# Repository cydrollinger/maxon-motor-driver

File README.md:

<a href="https://elec-real.com/case-studies/maxon-motor-driver/"></img></a>

>Electronic Realization L.L.C.								   
>Design: Maxon Motor Driver with Bluetooth v4.2/5.0		   
>Engineer: Cy Drollinger								   
>Date: 4/18												           
>Email: cy@elec-real.com
>Website: https://elec-real.com								   
>Address: 2023 Stadium Dr Suite 2B #210 Bozeman, MT 59715				   
>Phone: 406-539-8117	

**NOTE:**
 This case study has been tested and functions as specified. ER is a professional design house and monetary compensation is required for additional work toward this design enabling your monetary success, but conversation is welcome and appreciated toward improving any or all this design and its repository. 

 Think critically while operating and or redesigning this system. Open electronic circuitry can be dangerous due to easily shorting circuits which can generate immediate and intense heat resulting in fire. This is only one example of ill advised use. 			   

**PURPOSE:**
The puspose of this design was to implement a 3 phase DC motor driver for a high speed 8mm dia motor by
Maxon. The system utilizes the nRF52832 by Nordic Semicondutor which outputs bluetooth v4.2/5.0 wireless
communication. The device also boast the mpu9250 a 9 axis inertial sensor as well as a TDK's MEMs micro phone. 

>**File Arcitecture with a terse description**

* FOLDERS:
	* docs		: datasheets charging IC and battery holder
	* hardware	: eagle cadsoft(v7.7) hardware design files 	
		* library		: eagle part files 
		* manufacturing	: files required to produce the design
			* bom	: files created to order the parts	
			* gerber	: files generated to manufacture the board
			* <a href="https://oshpark.com/shared_projects/ryMoScdj"></img></a>
	* readme.md	: this file

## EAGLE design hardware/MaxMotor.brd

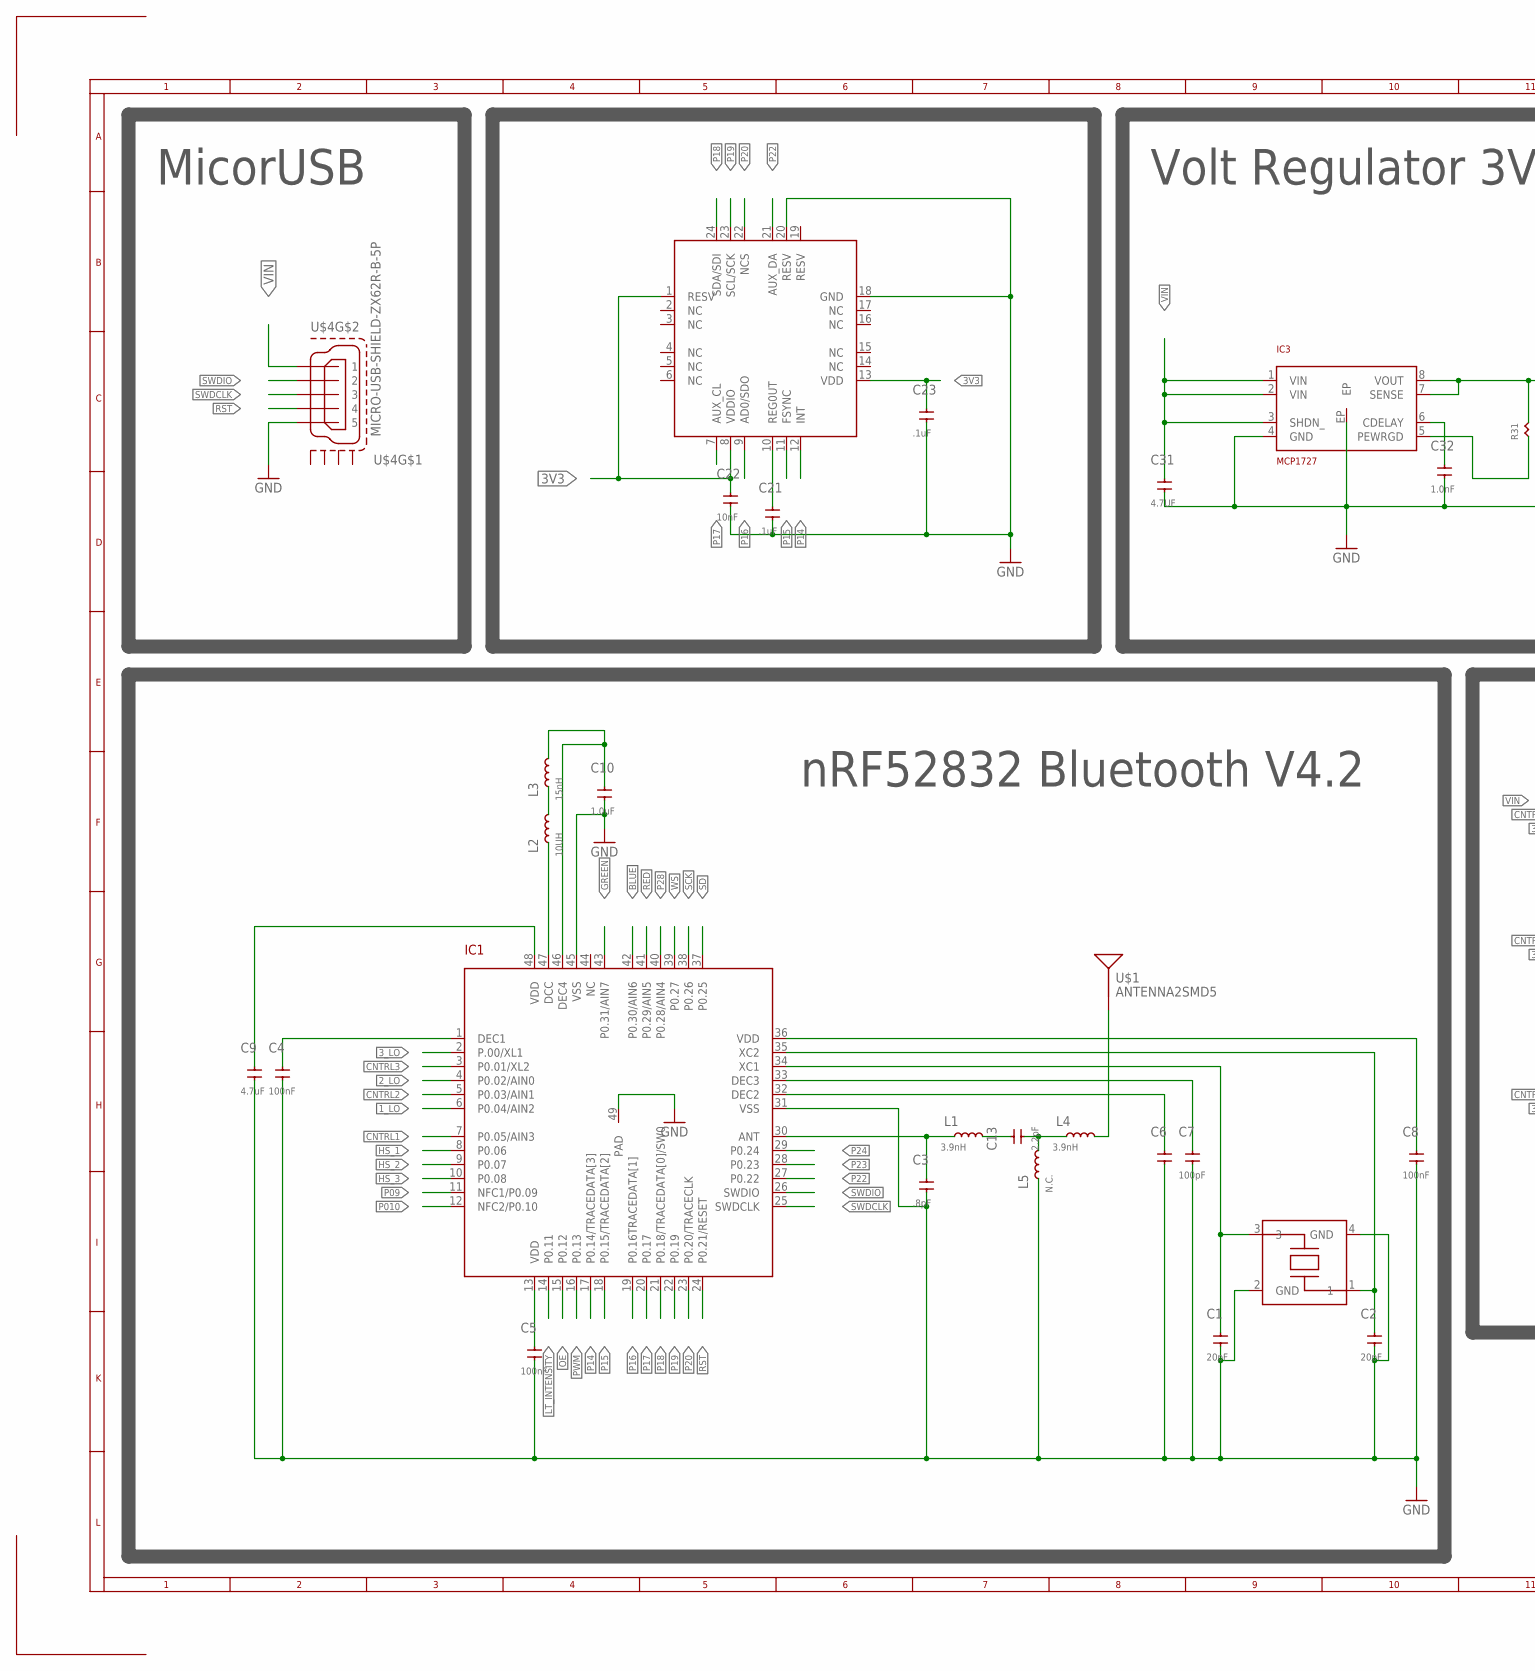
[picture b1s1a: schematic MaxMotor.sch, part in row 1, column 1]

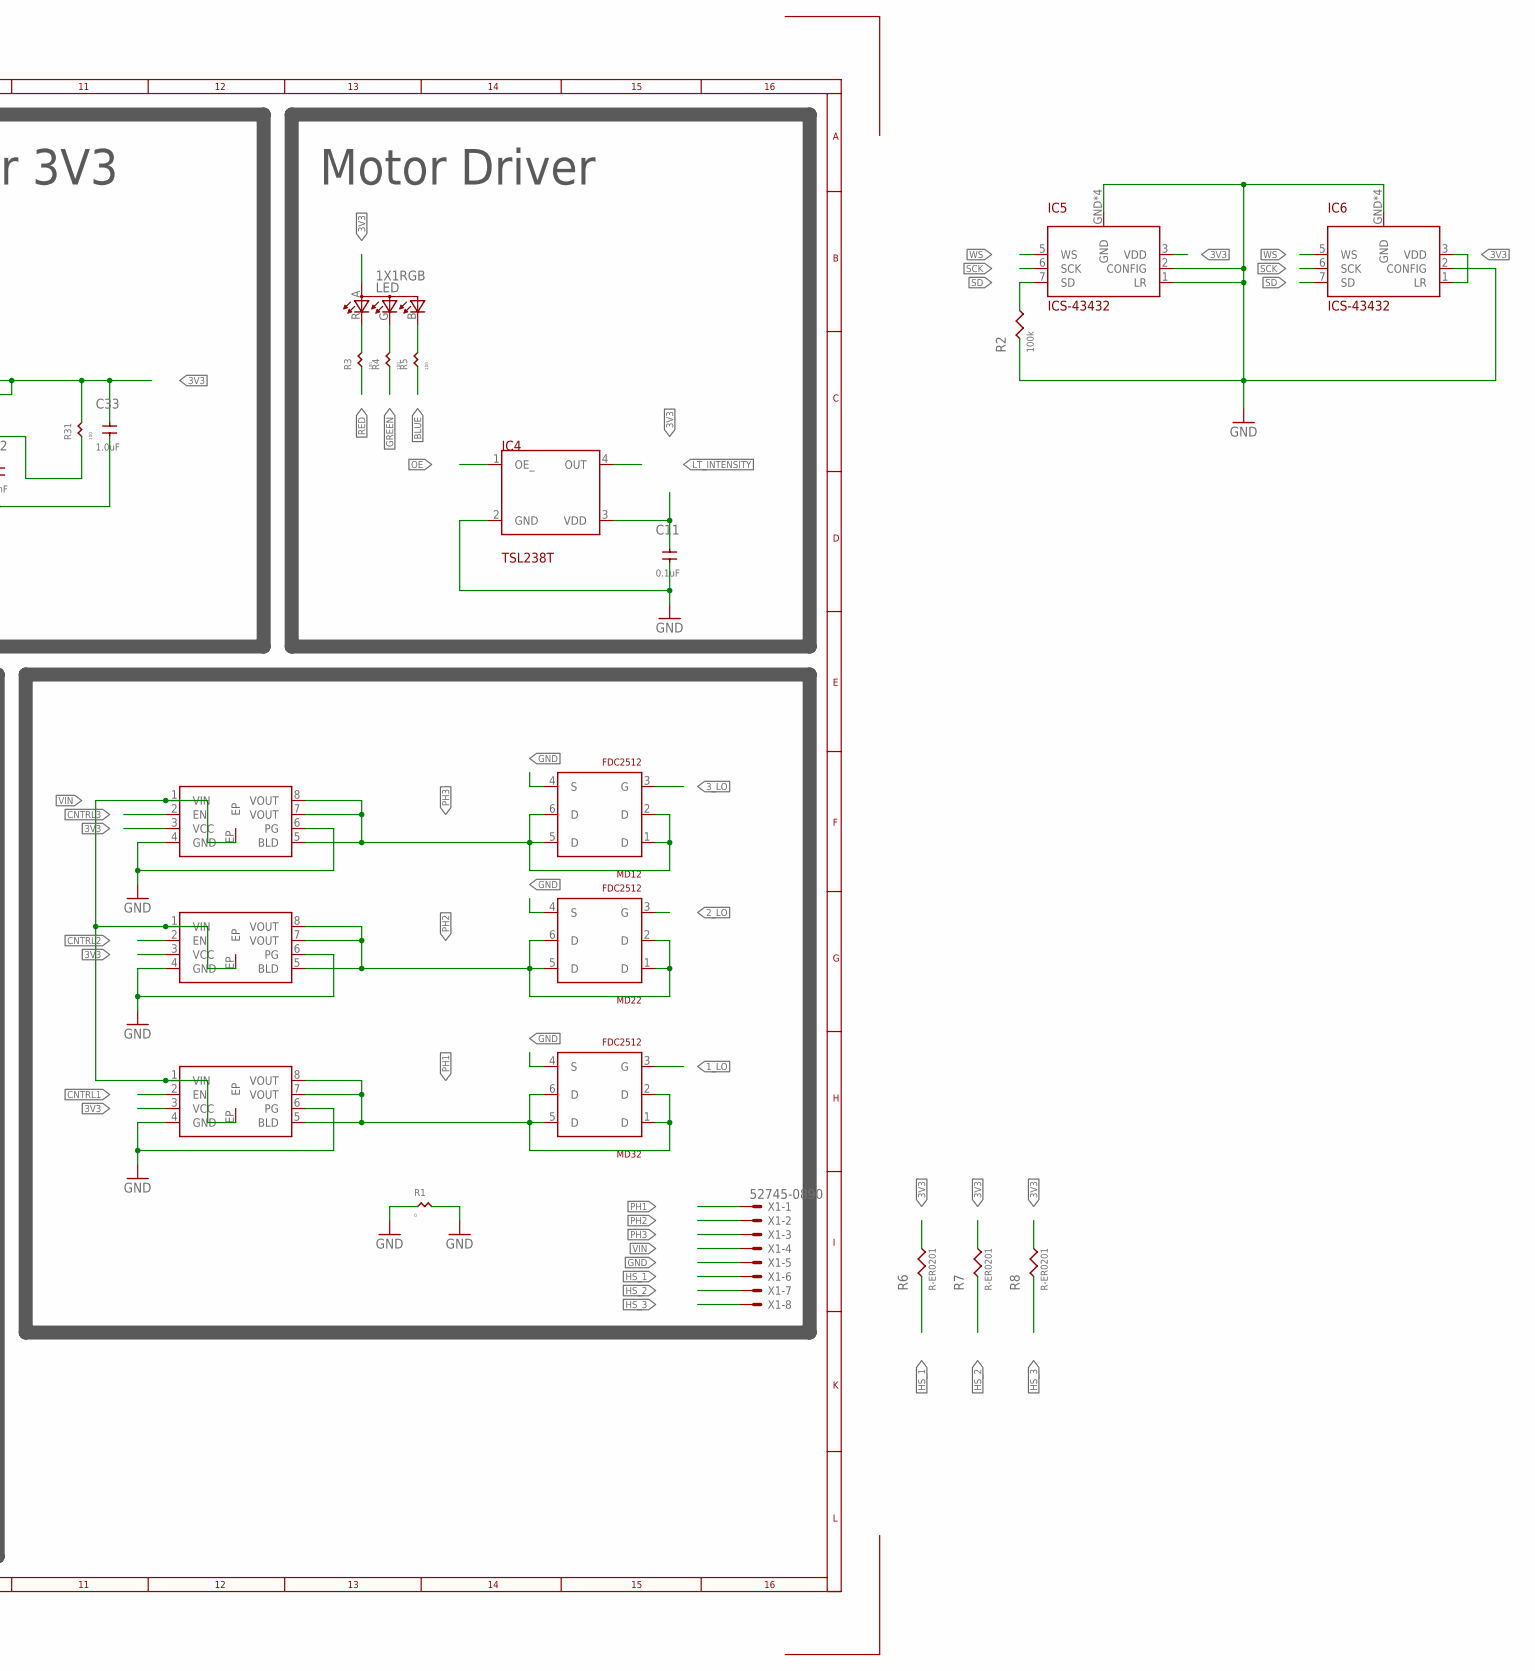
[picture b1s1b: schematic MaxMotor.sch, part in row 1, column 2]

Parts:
C1, C2: 20pF; C0402
C3: .8pF; C0402
C4, C5, C8: 100nF; C0402
C6: C-ERC0402; C0402
C7: 100pF; C0402
C9: 4.7uF; C0805
C10, C33: 1.0uF; C0402
C11: 0.1uF; C0402
C13: 2.2pF; C0402
C21, C23: .1uF; C0402
C22: 10nF; C0402
C31: 4.7UF; C0805
C32: 1.0nF; C0402
IC1: NRF52832; QFN48
IC2: MPU9250_CORRECTED; 3X3_24_QFN_CORRECTED
IC3: MCP1727; DFN8-3X3
IC4: TSL238T; T4
IC5, IC6: ICS-43432
L1, L4: 3.9nH; R0402
L2: 10UH; R0603
L3: 15nH; R0402
L5: N.C.; R0402
LED: 1X1RGB; 1X1
MD12, MD22, MD32: FDC2512; SSOT6
R1: 0; R0402
R2: 100k; R0402
R3, R4, R5, R31: 100; R0402
R6, R7, R8: R-ER0201; R0201
U$1: ANTENNA2SMD5; ANTENNA-CHIP5
U$2, U$5, U$6: NCP45524/25; DFN8
U$4: MICRO-USB-SHIELD-ZX62R-B-5P; ZX62R-B-5P
X1: 52745-0890
XTL16M: FA-128

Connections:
1_LO: IC1.6 (P0.04/AIN2), MD32.3 (G)
2_LO: IC1.4 (P0.02/AIN0), MD22.3 (G)
3V3: C5.2, C8.2, C9.2, C11.2, C22.2, C23.2, C33.2, IC1.13 (VDD), IC1.36 (VDD), IC1.48 (VDD), IC2.1 (RESV), IC2.8 (VDDIO), IC2.13 (VDD), IC3.7 (SENSE), IC3.8 (VOUT), IC4.3 (VDD), IC5.3 (VDD), IC6.1 (LR), IC6.3 (VDD), LED.A (A2), R6.2, R7.2, R8.2, R31.2, U$2.3 (VCC), U$5.3 (VCC), U$6.3 (VCC)
3_LO: IC1.2 (P.00/XL1), MD12.3 (G)
BLUE: IC1.42 (P0.30/AIN6), R5.1
CNTRL1: IC1.7 (P0.05/AIN3), U$6.2 (EN)
CNTRL2: IC1.5 (P0.03/AIN1), U$5.2 (EN)
CNTRL3: IC1.3 (P0.01/XL2), U$2.2 (EN)
GND: C1.1, C2.1, C3.1, C4.1, C5.1, C6.1, C7.1, C8.1, C9.1, C10.1, C11.1, C21.1, C22.1, C23.1, C31.1, C32.1, C33.1, IC1.31 (VSS), IC1.45 (VSS), IC1.49 (PAD), IC2.18 (GND), IC2.20 (RESV), IC3.4 (GND), IC3.EP, IC4.2 (GND), IC5.1 (LR), IC5.2 (CONFIG), IC5.GND, IC5.GND@ (GND), IC5.GND@1 (GND), IC5.GND@2 (GND), IC6.2 (CONFIG), IC6.GND, IC6.GND@ (GND), IC6.GND@1 (GND), IC6.GND@2 (GND), L5.1, MD12.4 (S), MD22.4 (S), MD32.4 (S), R1.1, R1.2, R2.1, U$2.4 (GND), U$2.6 (PG), U$4.1 (5), U$5.4 (GND), U$5.6 (PG), U$6.4 (GND), U$6.6 (PG), X1.5, XTL16M.2 (GND), XTL16M.4 (GND)
GREEN: IC1.43 (P0.31/AIN7), R4.1
HS_1: IC1.8 (P0.06), R6.1, X1.6
HS_2: IC1.9 (P0.07), R7.1, X1.7
HS_3: IC1.10 (P0.08), R8.1, X1.8
LT_INTENSITY: IC1.14 (P0.11), IC4.4 (OUT)
unnamed: C21.2, IC2.10 (REG0UT)
unnamed: C3.2, IC1.30 (ANT), L1.1
unnamed: C6.2, IC1.32 (DEC2)
unnamed: C13.2, L1.2
unnamed: C7.2, IC1.33 (DEC3)
unnamed: C1.2, IC1.34 (XC1), XTL16M.3
unnamed: C2.2, IC1.35 (XC2), XTL16M.1
unnamed: IC1.47 (DCC), L2.1
unnamed: L2.2, L3.1
unnamed: C10.2, IC1.46 (DEC4), L3.2
unnamed: LED.B (CGREEN), R5.2
unnamed: C13.1, L4.1, L5.2
unnamed: L4.2, U$1.FEED
unnamed: LED.G (CBLUE), R4.2
unnamed: IC3.5 (PEWRGD), R31.1
unnamed: LED.R (CRED), R3.2
unnamed: C32.2, IC3.6 (CDELAY)
unnamed: C4.2, IC1.1 (DEC1)
OE: IC1.15 (P0.12), IC4.1 (OE_)
P09: IC1.11 (NFC1/P0.09)
P010: IC1.12 (NFC2/P0.10)
P14: IC1.17 (P0.14/TRACEDATA[3]), IC2.12 (INT)
P15: IC1.18 (P0.15/TRACEDATA[2]), IC2.11 (FSYNC)
P16: IC1.19 (P0.16TRACEDATA[1]), IC2.9 (AD0/SDO)
P17: IC1.20 (P0.17), IC2.7 (AUX_CL)
P18: IC1.21 (P0.18/TRACEDATA[0]/SW0), IC2.24 (SDA/SDI)
P19: IC1.22 (P0.19), IC2.23 (SCL/SCK)
P20: IC1.23 (P0.20/TRACECLK), IC2.22 (NCS)
P22: IC1.27 (P0.22), IC2.21 (AUX_DA)
P23: IC1.28 (P0.23)
P24: IC1.29 (P0.24)
P28: IC1.40 (P0.28/AIN4)
PH1: MD32.1 (D), MD32.2 (D), MD32.5 (D), MD32.6 (D), U$6.5 (BLD), U$6.7 (VOUT), U$6.8 (VOUT), X1.1
PH2: MD22.1 (D), MD22.2 (D), MD22.5 (D), MD22.6 (D), U$5.5 (BLD), U$5.7 (VOUT), U$5.8 (VOUT), X1.2
PH3: MD12.1 (D), MD12.2 (D), MD12.5 (D), MD12.6 (D), U$2.5 (BLD), U$2.7 (VOUT), U$2.8 (VOUT), X1.3
PWM: IC1.16 (P0.13)
RED: IC1.41 (P0.29/AIN5), R3.1
RST: IC1.24 (P0.21/RESET), U$4.2 (4)
SCK: IC1.38 (P0.26), IC5.6 (SCK), IC6.6 (SCK)
SD: IC1.37 (P0.25), IC5.7 (SD), IC6.7 (SD), R2.2
SWDCLK: IC1.25 (SWDCLK), U$4.3
SWDIO: IC1.26 (SWDIO), U$4.4 (2)
VIN: C31.2, IC3.1 (VIN), IC3.2 (VIN), IC3.3 (SHDN_), U$2.1 (VIN), U$2.EP, U$4.5 (1), U$5.1 (VIN), U$5.EP, U$6.1 (VIN), U$6.EP, X1.4
WS: IC1.39 (P0.27), IC5.5 (WS), IC6.5 (WS)

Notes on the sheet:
nRF52832 Bluetooth V4.2
MicorUSB
Volt Regulator 3V3
Motor Driver

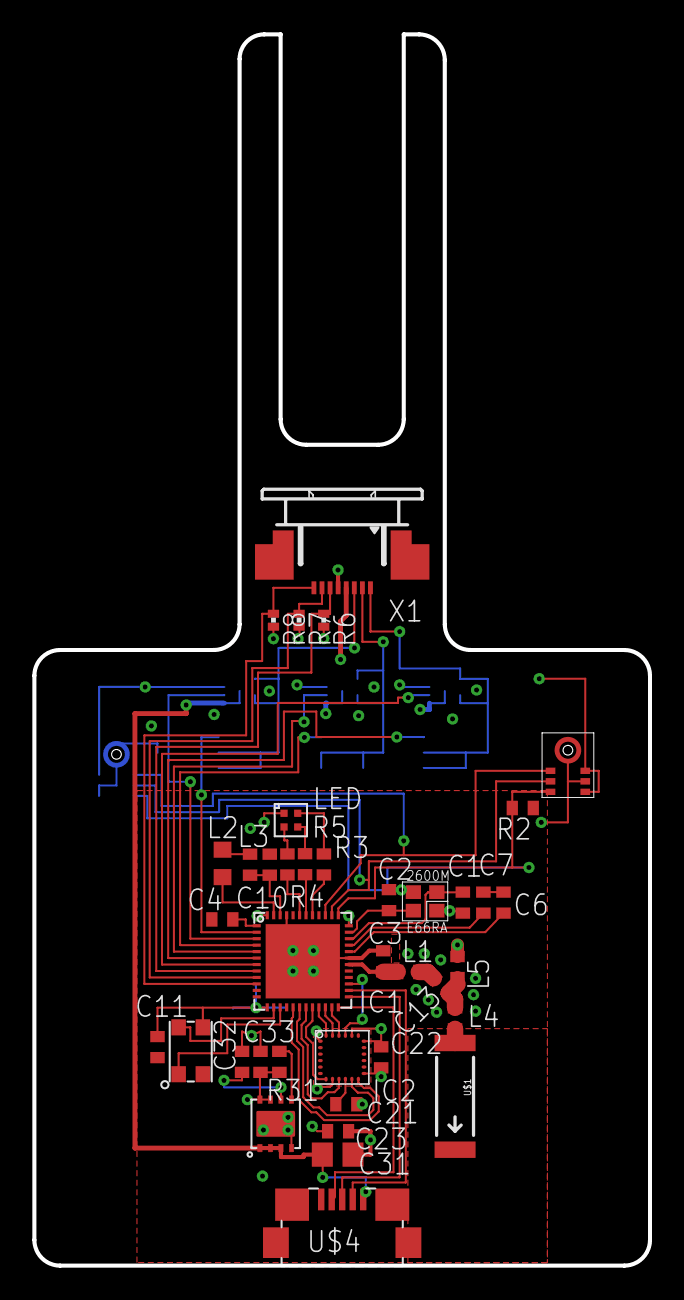
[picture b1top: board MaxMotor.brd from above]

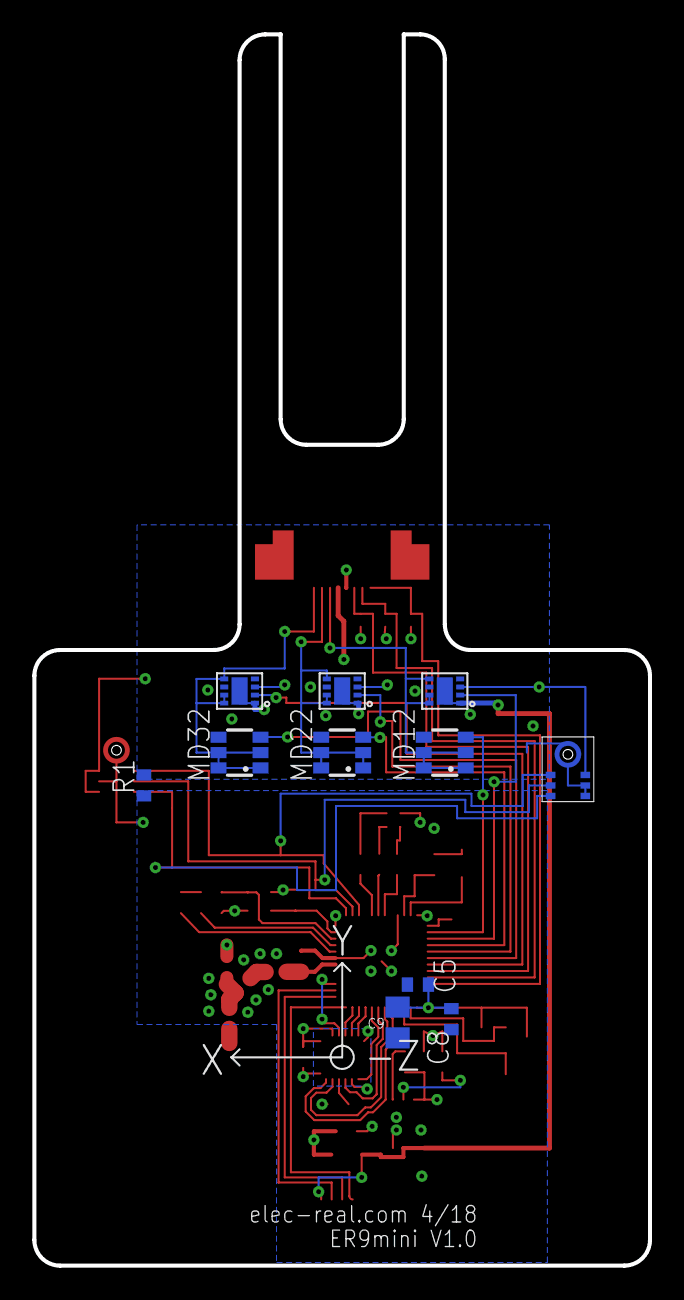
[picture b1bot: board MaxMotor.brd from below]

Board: 4 copper layers, 38.1 x 76.2 mm, 49 parts (11 on the bottom side), 52 nets.

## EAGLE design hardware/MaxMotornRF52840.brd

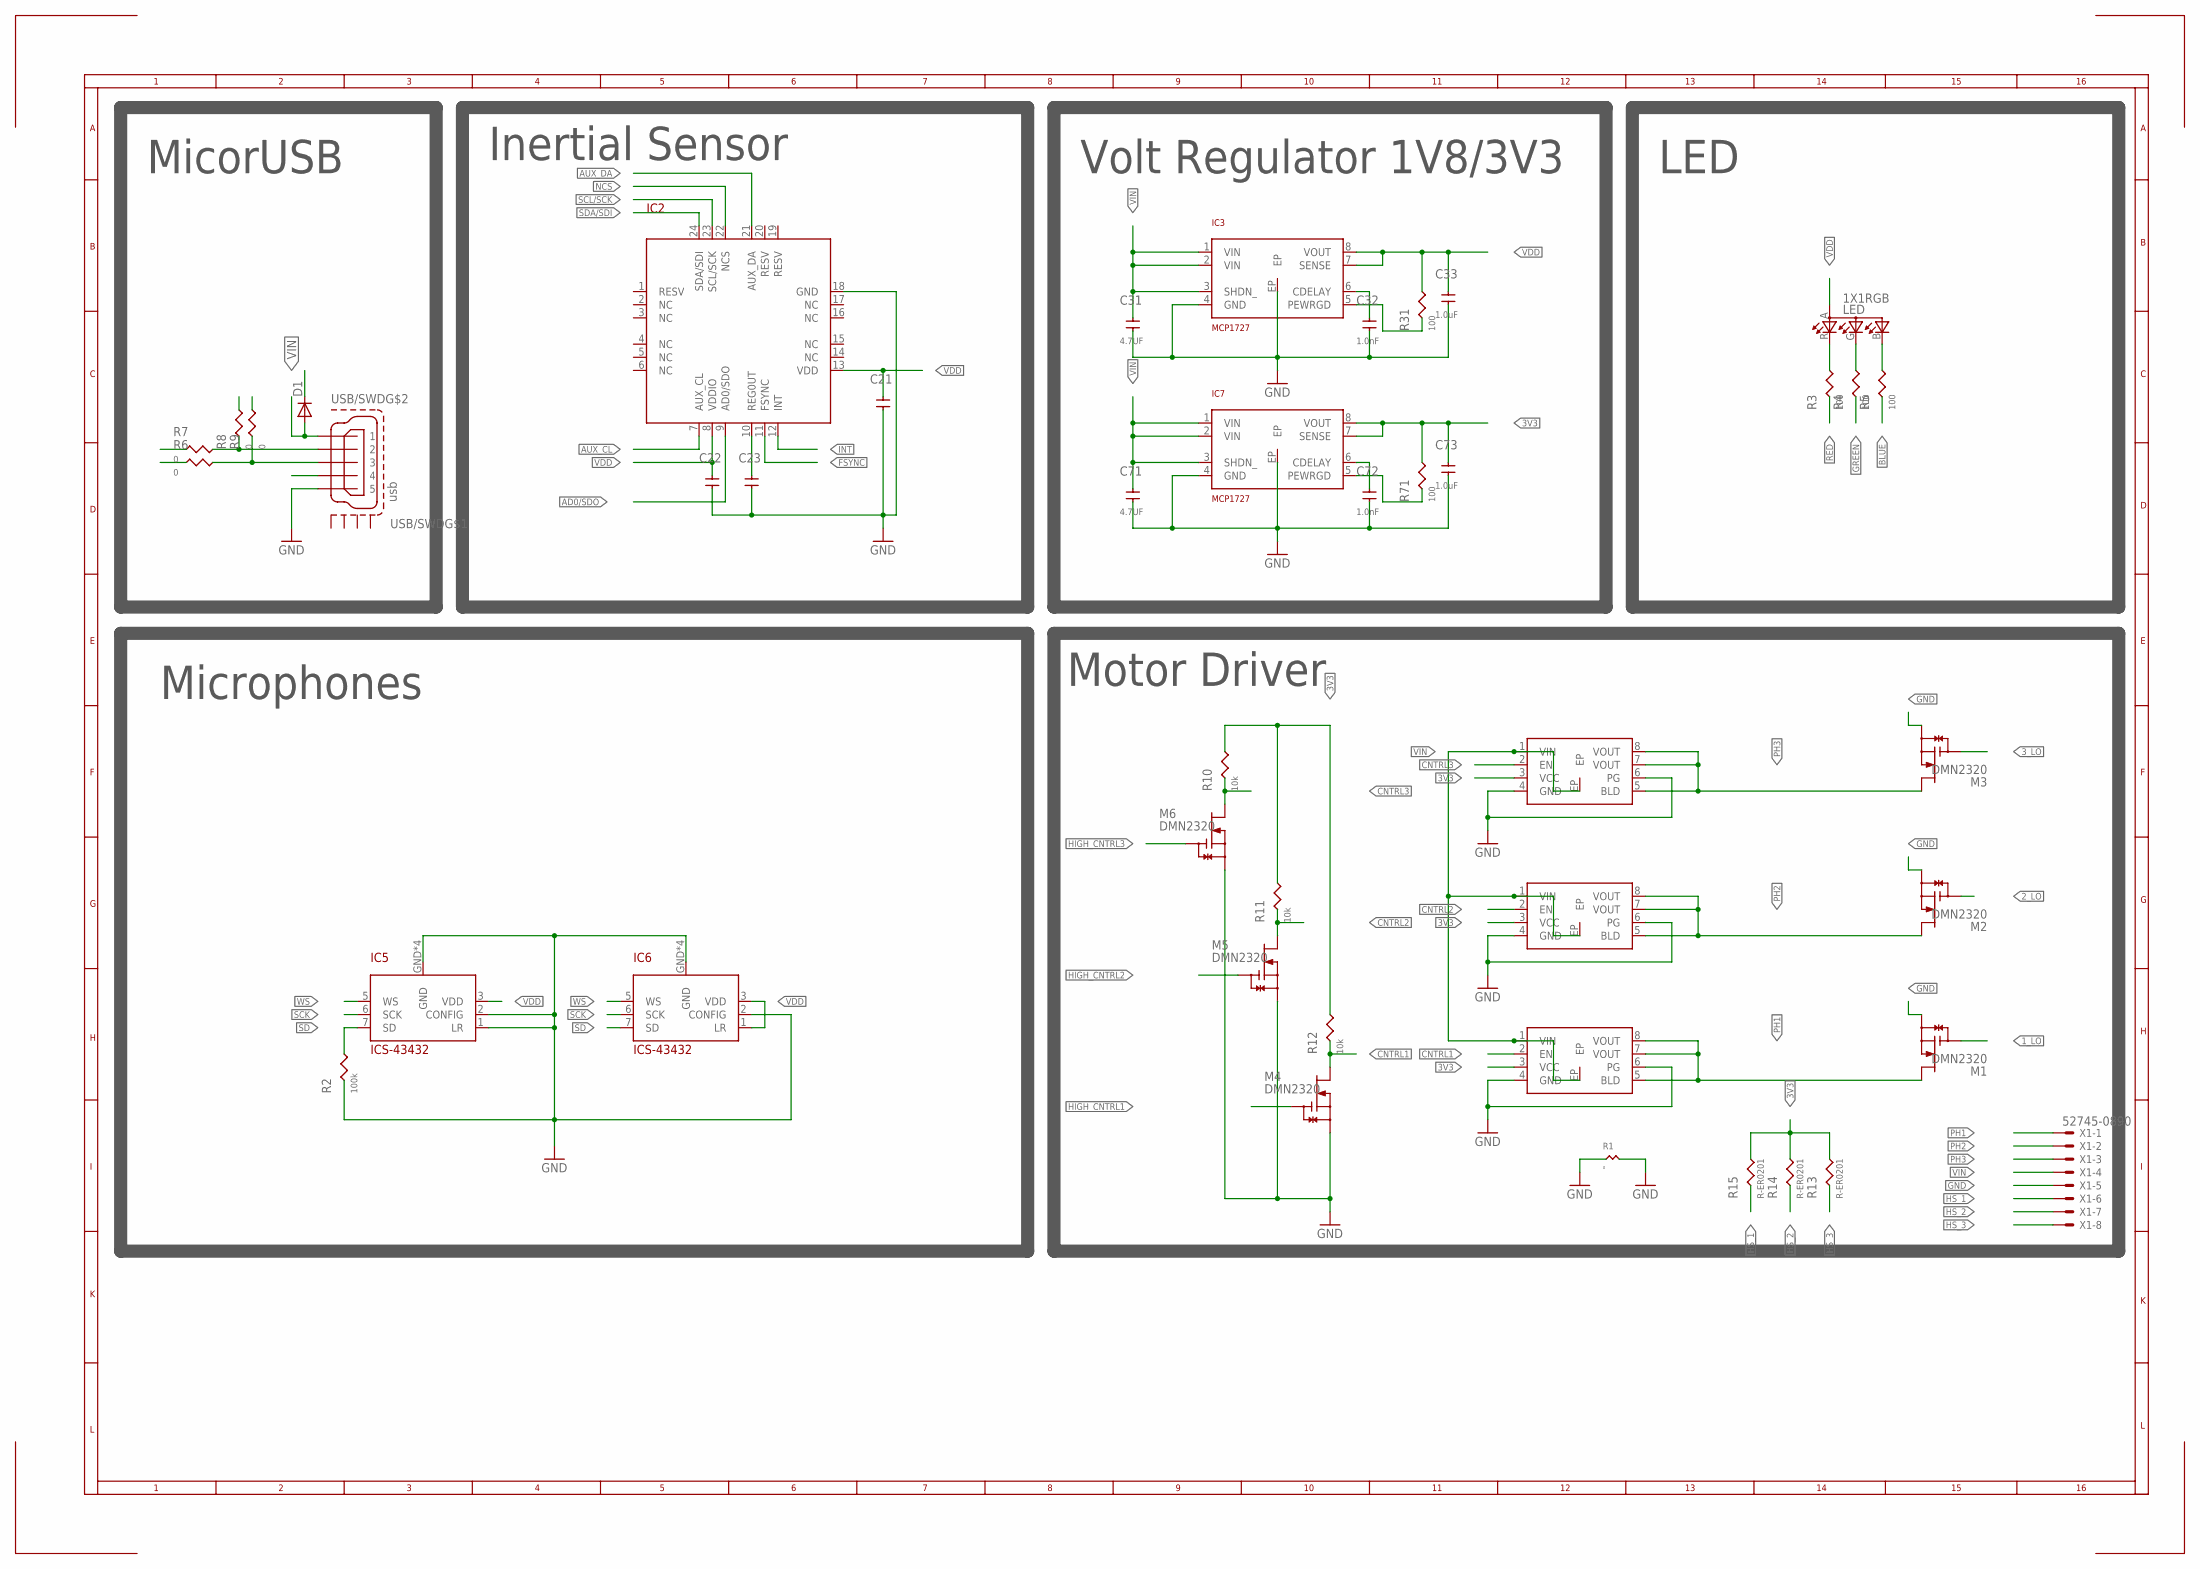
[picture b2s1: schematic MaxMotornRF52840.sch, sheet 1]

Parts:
C21, C22, C23: C-ER201; C0201
C31, C71: 4.7UF; C0402
C32, C72: 1.0nF; C0201
C33, C73: 1.0uF; C0201
D1: DIODE-SOD123; SOD123
IC2: ICM20948; 3X3_24_QFN_CORRECTED
IC3, IC7: MCP1727; DFN8-3X3
IC5, IC6: ICS-43432
LED: 1X1RGB; 1X1
M1, M2, M3, M4, M5, M6: DMN2320; AP02002
M7, M8, M9: NCP45524/25; DFN8
R1: 0; R0805
R2: 100k; R0201
R3, R4, R5, R31, R71: 100; R0201
R6, R7, R8, R9: 0; R0201
R10, R11, R12: 10k; R0201
R13, R14, R15: R-ER0201; R0201
USB/SWD: usb; ZX62R-B-5P
X1: 52745-0890

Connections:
1_LO: M1.G; also elsewhere on the board
2_LO: M2.G; also elsewhere on the board
3V3: C73.2, IC7.7 (SENSE), IC7.8 (VOUT), M7.3 (VCC), M8.3 (VCC), M9.3 (VCC), R10.2, R11.2, R12.2, R13.2, R14.2, R15.2, R71.2
3_LO: M3.G; also elsewhere on the board
AD0/SDO: IC2.9 (AD0/SDO); also elsewhere on the board
AUX_CL: IC2.7 (AUX_CL)
AUX_DA: IC2.21 (AUX_DA); also elsewhere on the board
BLUE: R5.1; also elsewhere on the board
CNTRL1: M4.D, M7.2 (EN), R12.1
CNTRL2: M5.D, M8.2 (EN), R11.1
CNTRL3: M6.D, M9.2 (EN), R10.1
D+: R6.1; also elsewhere on the board
D-: R7.1; also elsewhere on the board
FSYNC: IC2.11 (FSYNC); also elsewhere on the board
GND: C21.1, C22.1, C23.1, C31.1, C32.1, C33.1, C71.1, C72.1, C73.1, IC2.18 (GND), IC3.4 (GND), IC3.EP, IC5.1 (LR), IC5.2 (CONFIG), IC5.GND, IC5.GND@ (GND), IC5.GND@1 (GND), IC5.GND@2 (GND), IC6.2 (CONFIG), IC6.GND, IC6.GND@ (GND), IC6.GND@1 (GND), IC6.GND@2 (GND), IC7.4 (GND), IC7.EP, M1.S, M2.S, M3.S, M4.S, M5.S, M6.S, M7.4 (GND), M7.6 (PG), M8.4 (GND), M8.6 (PG), M9.4 (GND), M9.6 (PG), R1.1, R1.2, R2.1, USB/SWD.1 (5), X1.5; also elsewhere on the board
GREEN: R4.1; also elsewhere on the board
HIGH_CNTRL1: M4.G; also elsewhere on the board
HIGH_CNTRL2: M5.G; also elsewhere on the board
HIGH_CNTRL3: M6.G; also elsewhere on the board
HS_1: R15.1, X1.6; also elsewhere on the board
HS_2: R14.1, X1.7; also elsewhere on the board
HS_3: R13.1, X1.8; also elsewhere on the board
INT: IC2.12 (INT); also elsewhere on the board
unnamed: C23.2, IC2.10 (REG0UT)
unnamed: IC7.5 (PEWRGD), R71.1
unnamed: C72.2, IC7.6 (CDELAY)
unnamed: LED.B (CGREEN), R5.2
unnamed: LED.G (CBLUE), R4.2
unnamed: IC3.5 (PEWRGD), R31.1
unnamed: LED.R (CRED), R3.2
unnamed: C32.2, IC3.6 (CDELAY)
NCS: IC2.22 (NCS); also elsewhere on the board
PH1: M1.D, M7.5 (BLD), M7.7 (VOUT), M7.8 (VOUT), X1.1
PH2: M2.D, M8.5 (BLD), M8.7 (VOUT), M8.8 (VOUT), X1.2
PH3: M3.D, M9.5 (BLD), M9.7 (VOUT), M9.8 (VOUT), X1.3
RED: R3.1; also elsewhere on the board
SCK: IC5.6 (SCK), IC6.6 (SCK); also elsewhere on the board
SCL/SCK: IC2.23 (SCL/SCK); also elsewhere on the board
SD: IC5.7 (SD), IC6.7 (SD), R2.2; also elsewhere on the board
SDA/SDI: IC2.24 (SDA/SDI); also elsewhere on the board
SWDCLK: R9.2; also elsewhere on the board
SWDIO: R8.2; also elsewhere on the board
USB2: R7.2, R8.1, USB/SWD.4 (2)
USB3: R6.2, R9.1, USB/SWD.3
USB4: USB/SWD.2 (4)
VBUS: D1.C; also elsewhere on the board
VDD: C21.2, C22.2, C33.2, IC2.8 (VDDIO), IC2.13 (VDD), IC3.7 (SENSE), IC3.8 (VOUT), IC5.3 (VDD), IC6.1 (LR), IC6.3 (VDD), LED.A (A2), R31.2; also elsewhere on the board
VIN: C31.2, C71.2, D1.A, IC3.1 (VIN), IC3.2 (VIN), IC3.3 (SHDN_), IC7.1 (VIN), IC7.2 (VIN), IC7.3 (SHDN_), M7.1 (VIN), M7.EP, M8.1 (VIN), M8.EP, M9.1 (VIN), M9.EP, USB/SWD.5 (1), X1.4
WS: IC5.5 (WS), IC6.5 (WS); also elsewhere on the board

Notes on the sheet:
MicorUSB
Volt Regulator 1V8/3V3
LED
Motor Driver
Inertial Sensor
Microphones

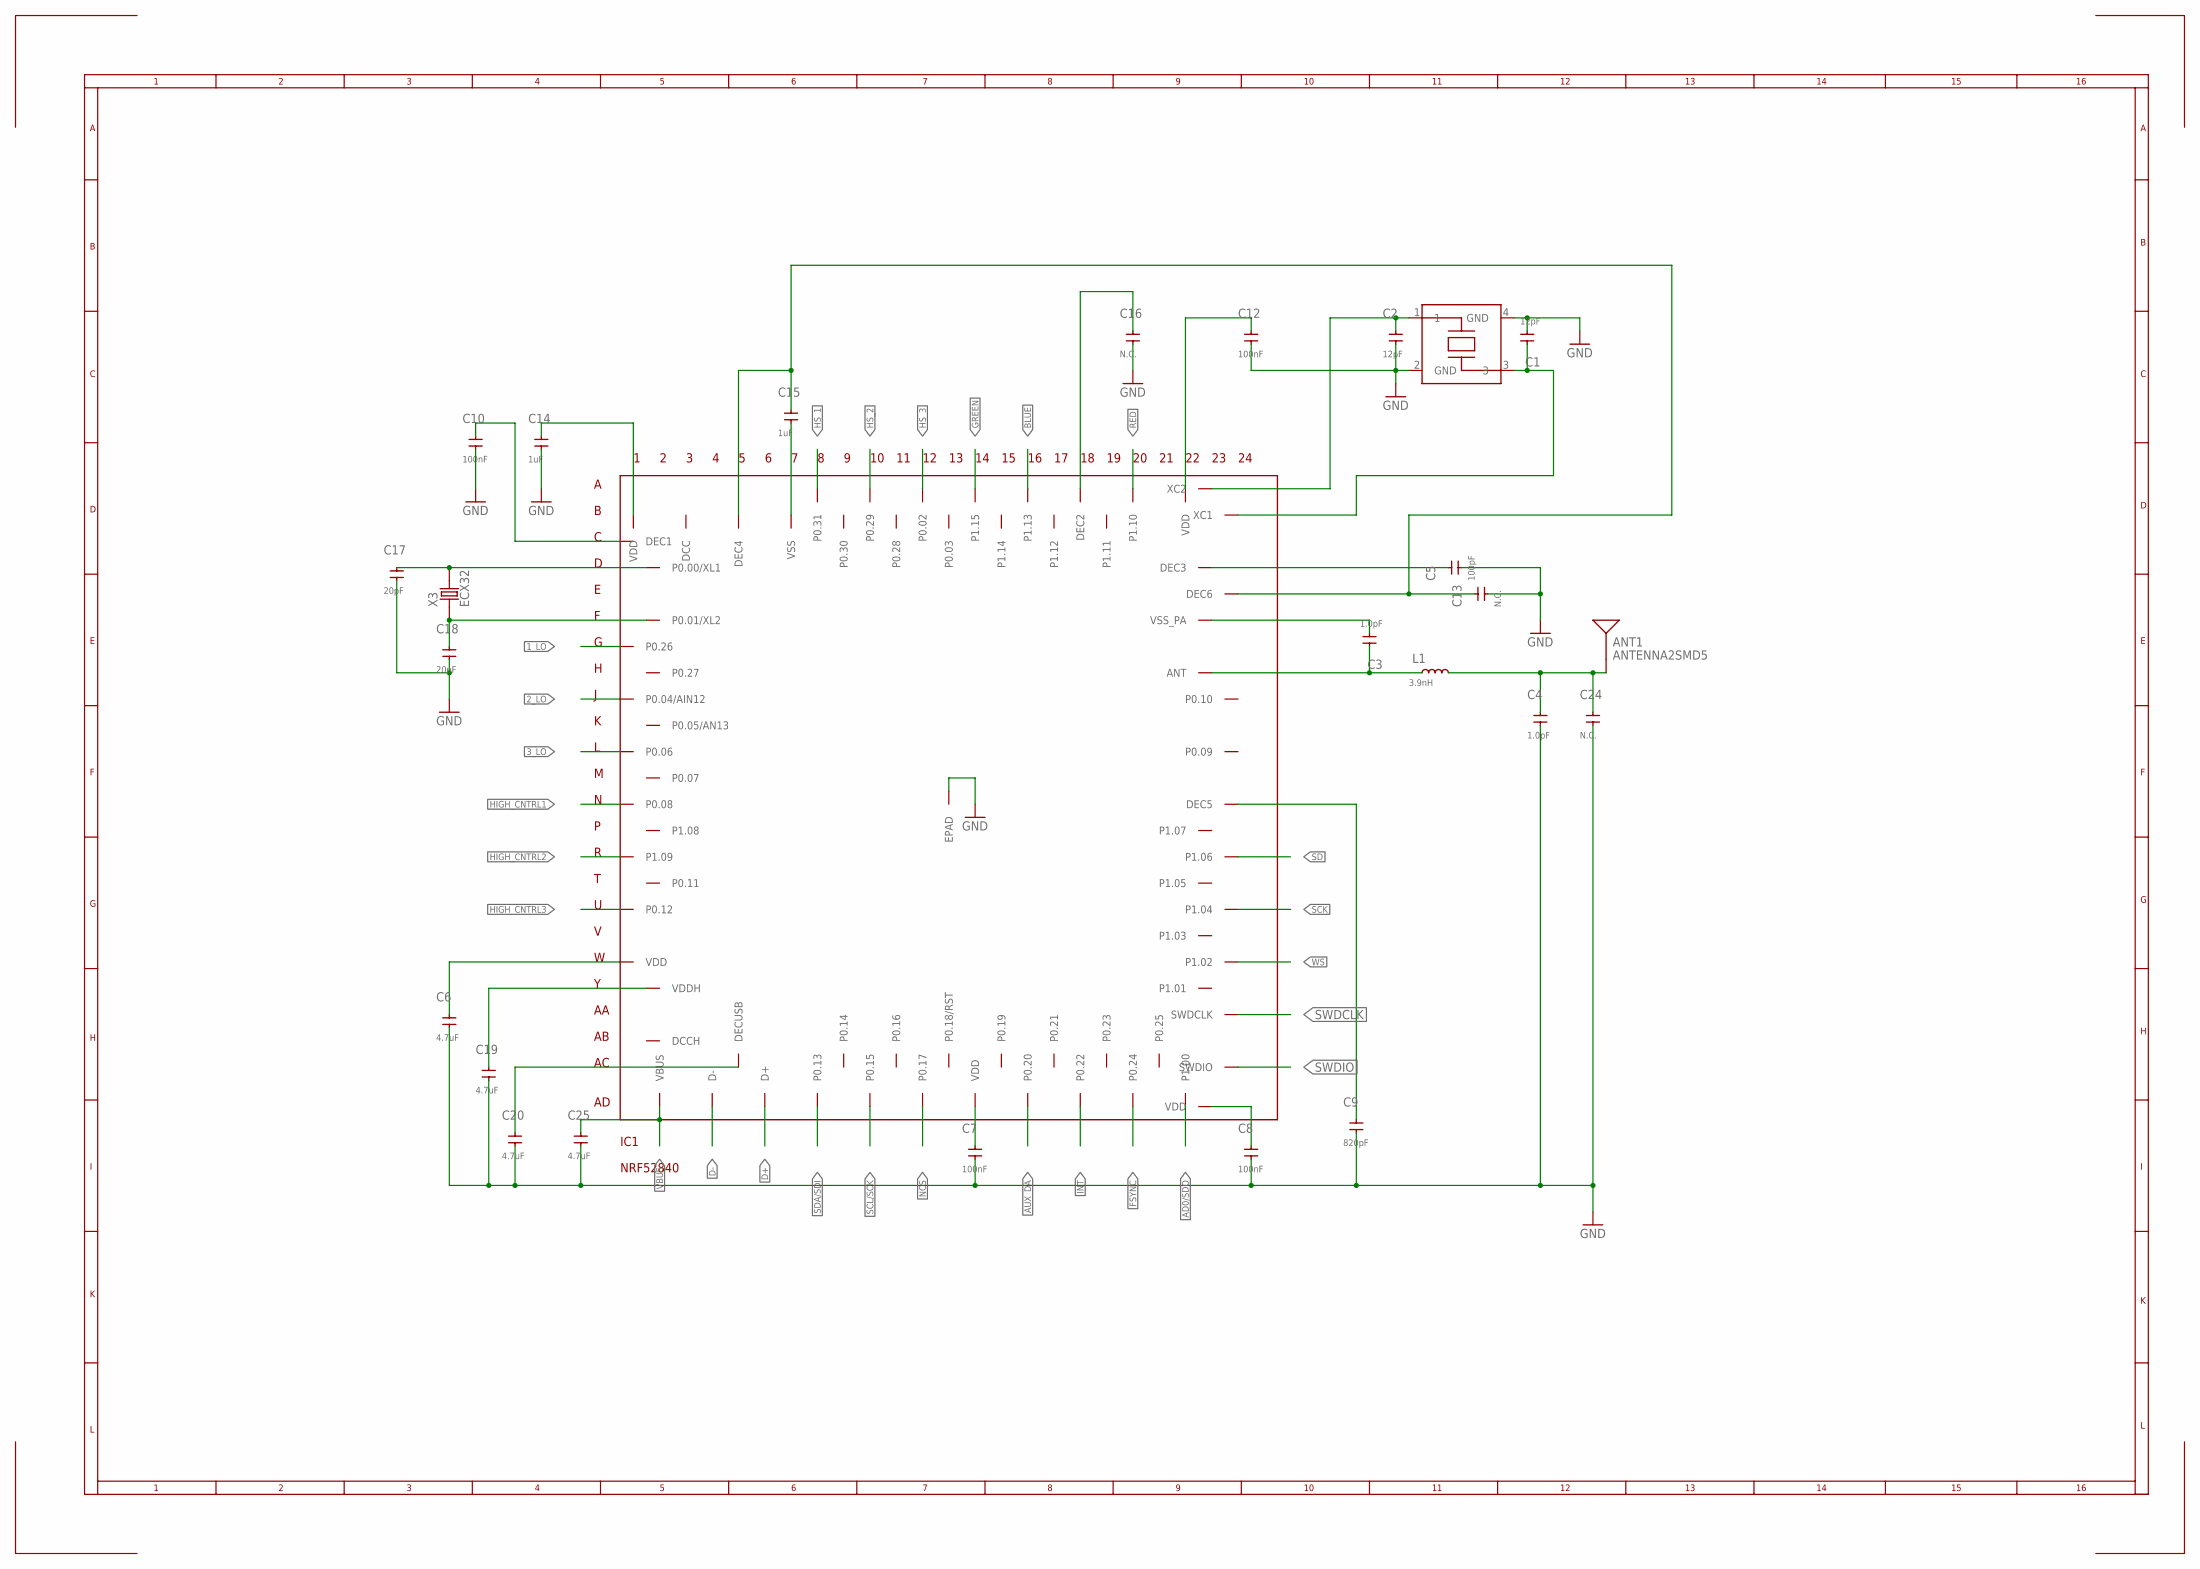
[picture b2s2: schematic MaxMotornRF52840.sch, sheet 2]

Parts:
ANT1: ANTENNA2SMD5; ANTENNA-CHIP5
C1, C2: 12pF; C0201
C3, C4: 1.0pF; C0201
C5: 100pF; C0201
C6, C19, C20, C25: 4.7uF; C0402
C7, C8, C10, C12: 100nF; C0201
C9: 820pF; C0201
C13, C16, C24: N.C.; C0201
C14, C15: 1uF; C0201
C17, C18: 20pF; C0201
IC1: NRF52840; AQFN73
L1: 3.9nH; C0201@1
X2: ABM12; DIGIKEY SER3800CT-ND
X3: ECX32; ECX39

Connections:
1_LO: IC1.G1 (P0.26); also elsewhere on the board
2_LO: IC1.J1 (P0.04/AIN12); also elsewhere on the board
3_LO: IC1.L1 (P0.06); also elsewhere on the board
AD0/SDO: IC1.AD22 (P1.00); also elsewhere on the board
AUX_DA: IC1.AD16 (P0.20); also elsewhere on the board
BLUE: IC1.A16 (P1.13); also elsewhere on the board
D+: IC1.AD6 (D+); also elsewhere on the board
D-: IC1.AD4 (D-); also elsewhere on the board
FSYNC: IC1.AD20 (P0.24); also elsewhere on the board
GND: C1.1, C2.1, C3.1, C4.1, C5.1, C6.1, C7.1, C8.1, C9.1, C10.1, C12.1, C13.1, C14.1, C15.1, C16.1, C17.1, C18.1, C19.1, C20.1, C24.1, C25.1, IC1.B7 (VSS), IC1.EPAD, IC1.F23 (VSS_PA), X2.2 (GND), X2.4 (GND); also elsewhere on the board
GREEN: IC1.A14 (P1.15); also elsewhere on the board
HIGH_CNTRL1: IC1.N1 (P0.08); also elsewhere on the board
HIGH_CNTRL2: IC1.R1 (P1.09); also elsewhere on the board
HIGH_CNTRL3: IC1.U1 (P0.12); also elsewhere on the board
HS_1: IC1.A8 (P0.31); also elsewhere on the board
HS_2: IC1.A10 (P0.29); also elsewhere on the board
HS_3: IC1.A12 (P0.02); also elsewhere on the board
INT: IC1.AD18 (P0.22); also elsewhere on the board
unnamed: C20.2, IC1.AC5 (DECUSB)
unnamed: C13.2, C15.2, IC1.B5 (DEC4), IC1.E24 (DEC6)
unnamed: C17.2, IC1.D2 (P0.00/XL1), X3.P$2 (2)
unnamed: C16.2, IC1.A18 (DEC2)
unnamed: C3.2, IC1.H23 (ANT), L1.1
unnamed: ANT1.FEED, C4.2, C24.2, L1.2
unnamed: C18.2, IC1.F2 (P0.01/XL2), X3.P$1 (1)
unnamed: C9.2, IC1.N24 (DEC5)
unnamed: C14.2, IC1.B1 (VDD)
unnamed: C5.2, IC1.D23 (DEC3)
NCS: IC1.AD12 (P0.17); also elsewhere on the board
RED: IC1.A20 (P1.10); also elsewhere on the board
SCK: IC1.U24 (P1.04); also elsewhere on the board
SCL/SCK: IC1.AD10 (P0.15); also elsewhere on the board
SD: IC1.R24 (P1.06); also elsewhere on the board
SDA/SDI: IC1.AD8 (P0.13); also elsewhere on the board
SWDCLK: IC1.AA24 (SWDCLK); also elsewhere on the board
SWDIO: IC1.AC24 (SWDIO); also elsewhere on the board
VBUS: C19.2, C25.2, IC1.AD2 (VBUS), IC1.Y2 (VDDH); also elsewhere on the board
VDD: C6.2, C7.2, C8.2, C10.2, C12.2, IC1.A22 (VDD), IC1.AD14 (VDD), IC1.AD23 (VDD), IC1.C1 (DEC1), IC1.W1 (VDD); also elsewhere on the board
WS: IC1.W24 (P1.02); also elsewhere on the board
XC1: C1.2, IC1.B24 (XC1), X2.3
XC2: C2.2, IC1.A23 (XC2), X2.1

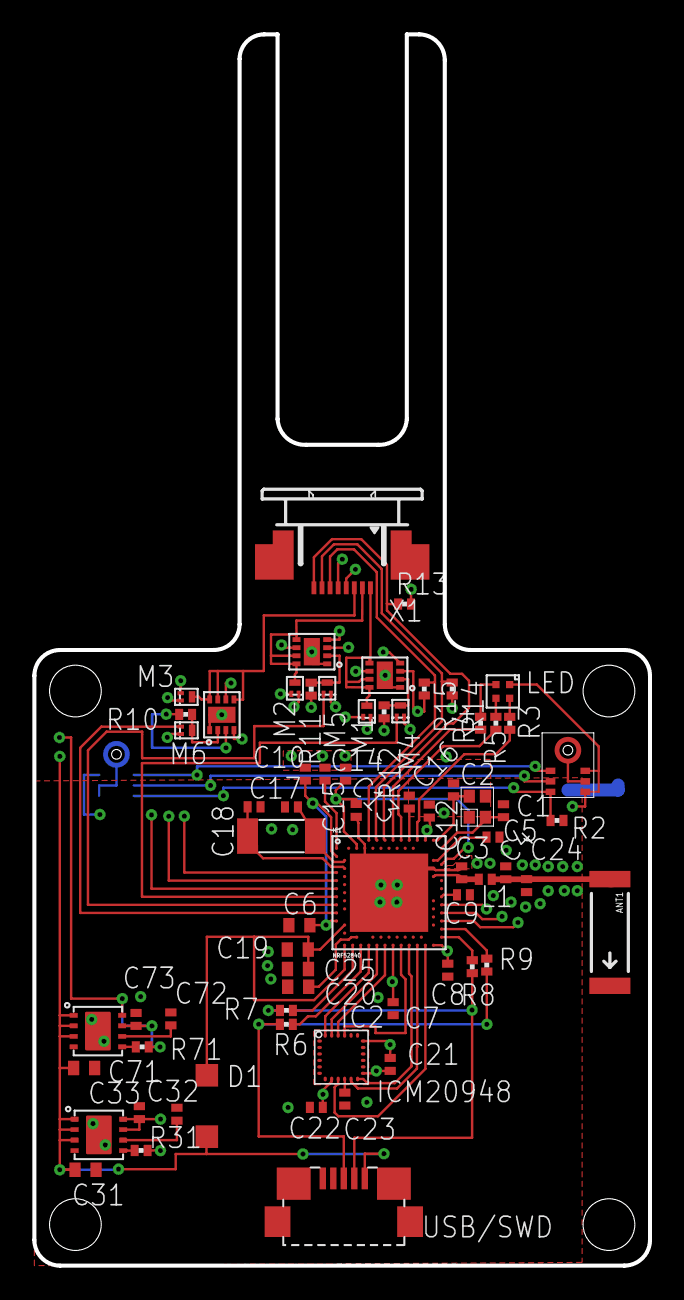
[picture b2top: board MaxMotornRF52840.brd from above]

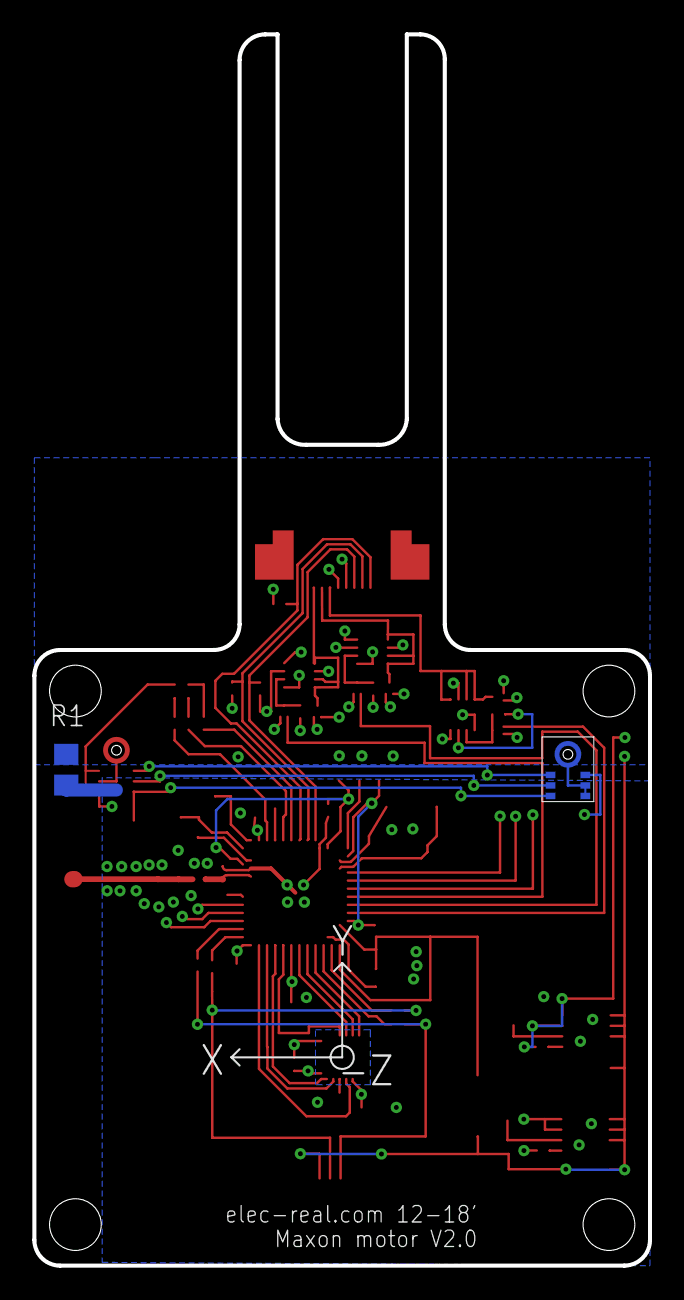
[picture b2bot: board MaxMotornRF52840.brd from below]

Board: 4 copper layers, 38.1 x 76.2 mm, 70 parts (2 on the bottom side), 59 nets.

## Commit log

2019-04-18 first commit 4/18/19
2019-04-26 first commit 4/26/19
2019-04-27 first commit 4/27/19
2019-04-30 first commit 4/30/19
